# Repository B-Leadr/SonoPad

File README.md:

# SonoPad
A macro keyboard for managing a system's sound.

## Features:
- 2x4 matrix of buttons
  - Default configuration for basic sound controls (can be customized in keymap)
- Rotary encoder for volume control
- 0.91" Oled Display

## Enclosure:
- Consists of a base and top plate part that are fastened with 4 M3x5mx4mm heatset inserts and 4 M3x16mm screws
- Base has a 15 degree tilt
- Both parts can be 3D printed
- Printed Knob for Rotary Encoder

## PCB:
- Wiring is simple as all the pullups and power supply are handling on the Speed xiao Rp2040 dev board
- The xiao rp2040 is placed on the back to allow space for the oled panel on the front. They overlap, but by raising the xiao off the back of the board with headers, there should be enough space to allow for both components as long as they are soldered on in the correct order
- Production files are for JLBPCB

## Firmware:
- [QMK](https://qmk.fm/) is used for the configuration, building, and flashing the firmware
- Rotary encoder controls volume
- Oled displays whatever you want (Need to add more features to this possibly multiple keymap layers and display of the current layer)
- All 8 keys map to different keys relating to sound control (Need to add more unique macros)

## BOM:
- 1x XIAO rp2040
- 1x EC11 Rotary Encoder
- 1x 0.91" 128x32 OLED SSD1306 Display
- 8x Cherry MX Switches
- 8x 1N4148 Diodes
- 8x DSA Keycaps
- 4x M3x4mm Screws
- 4x M3x5x4 Heatset Inserts
- 1x Case (2 printed parts)
- 1x Knob (Printed)
- 1x PCB (Etched by JLBPCB)

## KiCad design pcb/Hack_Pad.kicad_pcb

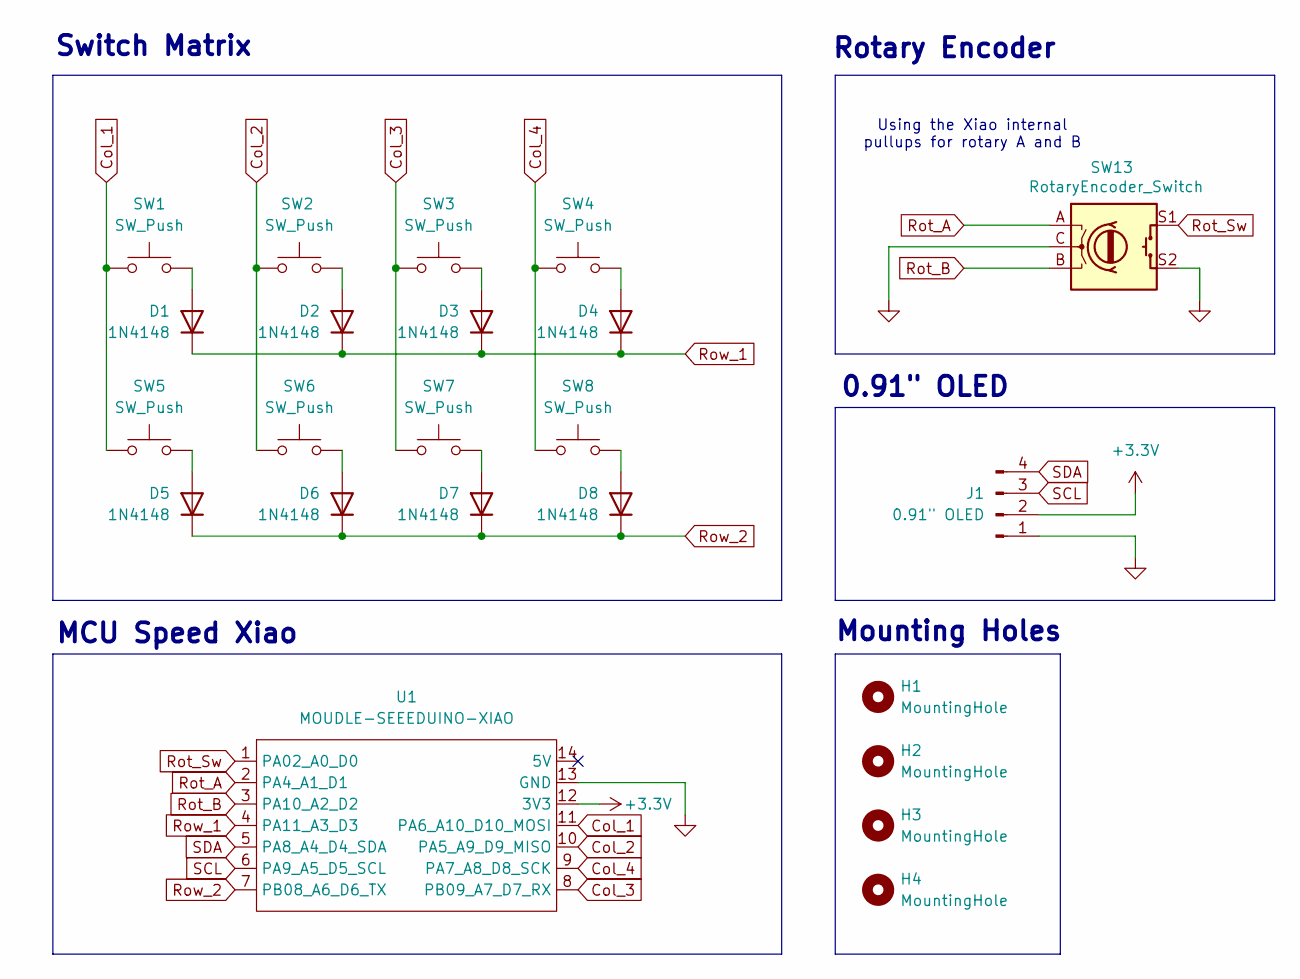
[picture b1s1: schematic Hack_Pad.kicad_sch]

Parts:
D1, D2, D3, D4, D5, D6, D7, D8: 1N4148; D_DO-35_SOD27_P7.62mm_Horizontal
H1, H2, H3, H4: MountingHole; MountingHole_2.2mm_M2
J1: 0.91" OLED; ER_OLEDM0.91_1x-I2C
SW1, SW2, SW3, SW4, SW5, SW6, SW7, SW8: SW_Push; SW_Cherry_MX_1.00u_PCB
SW13: RotaryEncoder_Switch; RotaryEncoder_Alps_EC11E-Switch_Vertical_H20mm
U1: MOUDLE-SEEEDUINO-XIAO; XIAO-Generic-Hybrid-14P-2.54-21X17.8MM

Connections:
+3.3V: J1.2, U1.12 (3V3)
Col_1: SW1.1, SW5.1, U1.11 (PA6_A10_D10_MOSI)
Col_2: SW2.1, SW6.1, U1.10 (PA5_A9_D9_MISO)
Col_3: SW3.1, SW7.1, U1.8 (PB09_A7_D7_RX)
Col_4: SW4.1, SW8.1, U1.9 (PA7_A8_D8_SCK)
GND: J1.1, SW13.C, SW13.S2, U1.13 (GND)
unnamed: D1.2 (A), SW1.2
unnamed: D2.2 (A), SW2.2
unnamed: D3.2 (A), SW3.2
unnamed: D4.2 (A), SW4.2
unnamed: D5.2 (A), SW5.2
unnamed: D6.2 (A), SW6.2
unnamed: D7.2 (A), SW7.2
unnamed: D8.2 (A), SW8.2
Rot_A: SW13.A, U1.2 (PA4_A1_D1)
Rot_B: SW13.B, U1.3 (PA10_A2_D2)
Rot_Sw: SW13.S1, U1.1 (PA02_A0_D0)
Row_1: D1.1 (K), D2.1 (K), D3.1 (K), D4.1 (K), U1.4 (PA11_A3_D3)
Row_2: D5.1 (K), D6.1 (K), D7.1 (K), D8.1 (K), U1.7 (PB08_A6_D6_TX)
SCL: J1.3, U1.6 (PA9_A5_D5_SCL)
SDA: J1.4, U1.5 (PA8_A4_D4_SDA)

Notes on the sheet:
0.91" OLED
Using the Xiao internal pullups for rotary A and B
Switch Matrix
Mounting Holes
MCU Speed Xiao
Rotary Encoder

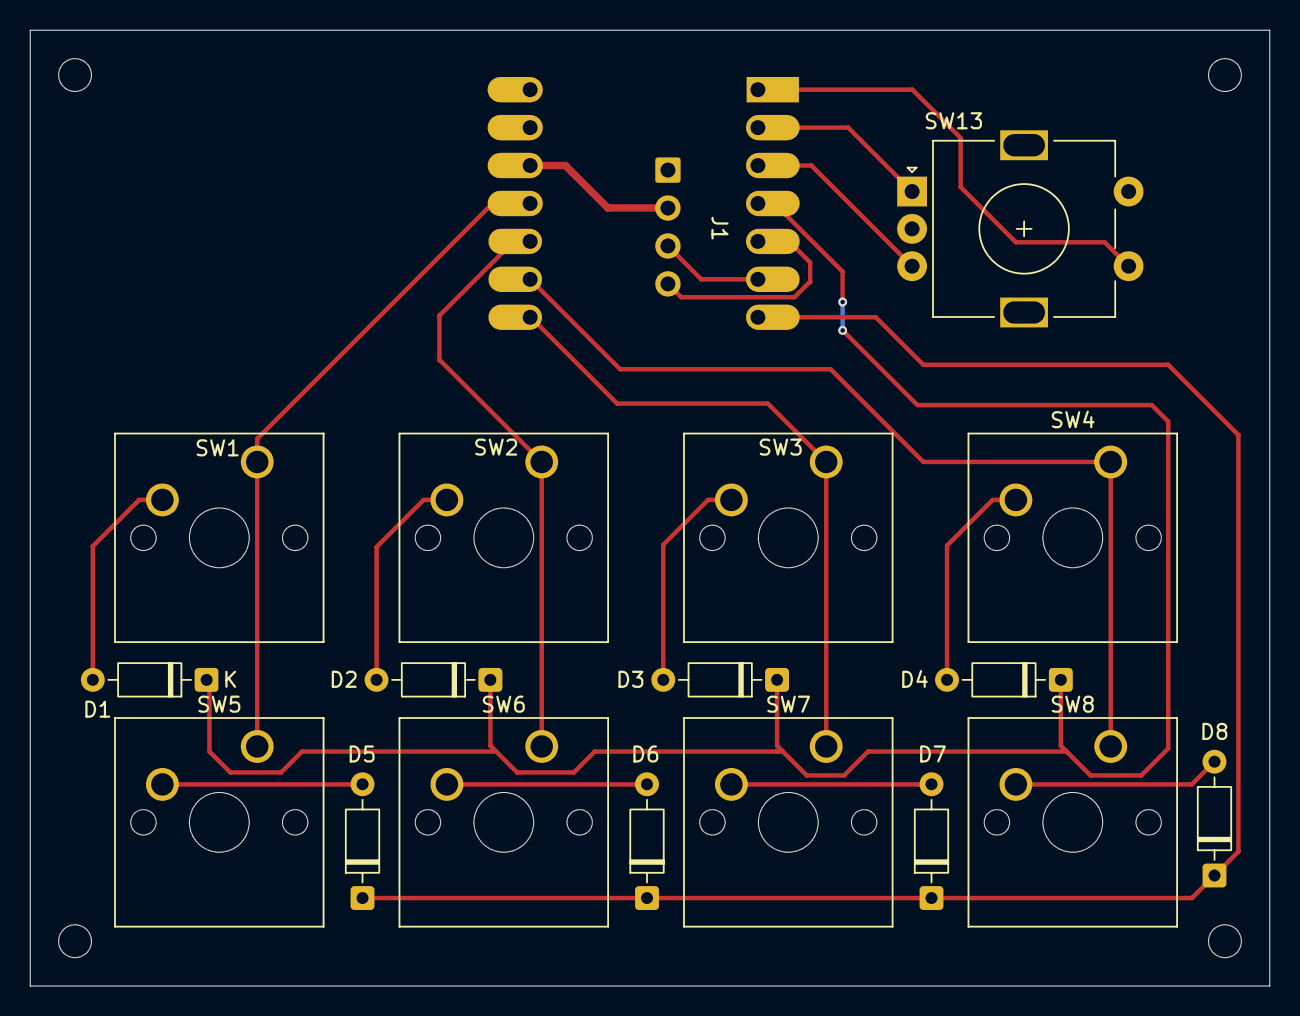
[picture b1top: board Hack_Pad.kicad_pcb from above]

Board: 2 copper layers, 83.0 x 64.0 mm, 23 parts (1 on the bottom side), 21 nets.

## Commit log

2026-06-17 Added Kicad project files
2026-06-18 Added production, cad, and firmware files
2026-06-18 Updated Readme with features, pictures, pcb, firmware, and BOM sections
    Expanded the README with detailed features, enclosure, PCB, firmware, and BOM information.
2026-06-18 Fixed Readme formating
2026-06-18 Updated case step to have place holder pcb
2026-06-18 Added BOM ins csv
2026-06-19 Updated Cad model
2026-06-19 Updated photo
    Updated the README to include a printed knob for the rotary encoder and corrected screw specifications.
